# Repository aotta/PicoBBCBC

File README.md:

# PicoBBCBC
A BBC Bridge Companion Multicart based on Pico clone

This project allows you to bypass the original system constraints and load multiple ROMs onto the console using an interactive Z80 Assembly frontend menu and smart address-bus monitoring for seamless bank-switching.

---

## Hardware Gallery

Here is the hardware implementation of the multicart PCB and assembly:

| Cartridge PCB | Fully Assembled Unit |
|:---:|:---:|
|  |  |

*(Note: Please ensure your image filenames inside the `pictures/` folder match `pcb.jpg` and `assembled.jpg`, or update the paths above accordingly!)*

---

## How It Works

1. **The Z80 Frontend Menu**: Upon boot, a custom splash screen and menu written in pure Z80 Assembly initializes the TMS9129 VDP (Video Display Processor) and the Z80PIO chip.
2. **Menu Navigation**: The console's dedicated keyboard matrix is scanned continuously.
   * Press **PASS** to scroll **UP**.
   * Press **SPADES ** to scroll **DOWN**.
   * Press **CLUBS (** to **SELECT/START** the highlighted game.
3. **Address-Bus Triggering**: Once a game is selected, the cursor flashes as a confirmation feedback. The Z80 CPU then enters a tight loop, constantly reading from a specific ROM address range:
   \[\text{Target Address} = \$5000 + \text{Game Index (0-8)}\]
4. **Pico Bank-Switching**: The Raspberry Pi Pico acts as a bus sniffer. It detects the continuous read cycles (`MREQ` and `RD` active) on the targeted address within the `$7000–$7008` window. It instantly switches the memory bank to the selected game ROM and triggers a hardware reset to boot the new title.

---
## IMPORTANT NOTE: by mistake, I designed the edge connector REVERSED, so the cartridge *MUST* be inserted with pico facing down!

## Project Structure

The repository is organized as follows:
* `/PicoBBCBC`: Contains the `.ino` firmware source code for the Raspberry Pi Pico.
* `/PCB`: Contains the design files, schematics, and layouts for manufacturing the custom cartridge board.
* `/roms`: Storage directory for compiling and organizing the game binary files.
* `/pictures`: Images and visual documentation of the project.

---

## Compilation & Installation

### Z80 Menu Compilation
To assemble the menu source code (`splash.asm`), use the `gasm80` assembler:
```bash
gasm80 splash.asm -o splash.bin
```

### Pico Firmware
1. First time, flash must be formatted and ROM loaded. So, only the first time, you must upoad on pico the FW **`PicoBBCBC_FirstRun.uf2`**.
2. Format the flash RAM when asked by window and then load the ROMs **with the same name i used in the ROM folder** (the filenames are hardcoded in FW).
3. Now, you have to **reflash the Pico with the FW ad on pico the FW **`PicoBBCBC.ino.uf2`**.
4. Enjoy your multicart.

---

## License
This project is licensed under the GPL-3.0 License - see the [LICENSE](LICENSE) file for details.

## Acknowledgments
* Special thanks to **Leaded Solder** for the extensive reverse engineering documentation on the BBC Bridge Companion VDP registers, Z80PIO matrix structures, and stack pointer layout.

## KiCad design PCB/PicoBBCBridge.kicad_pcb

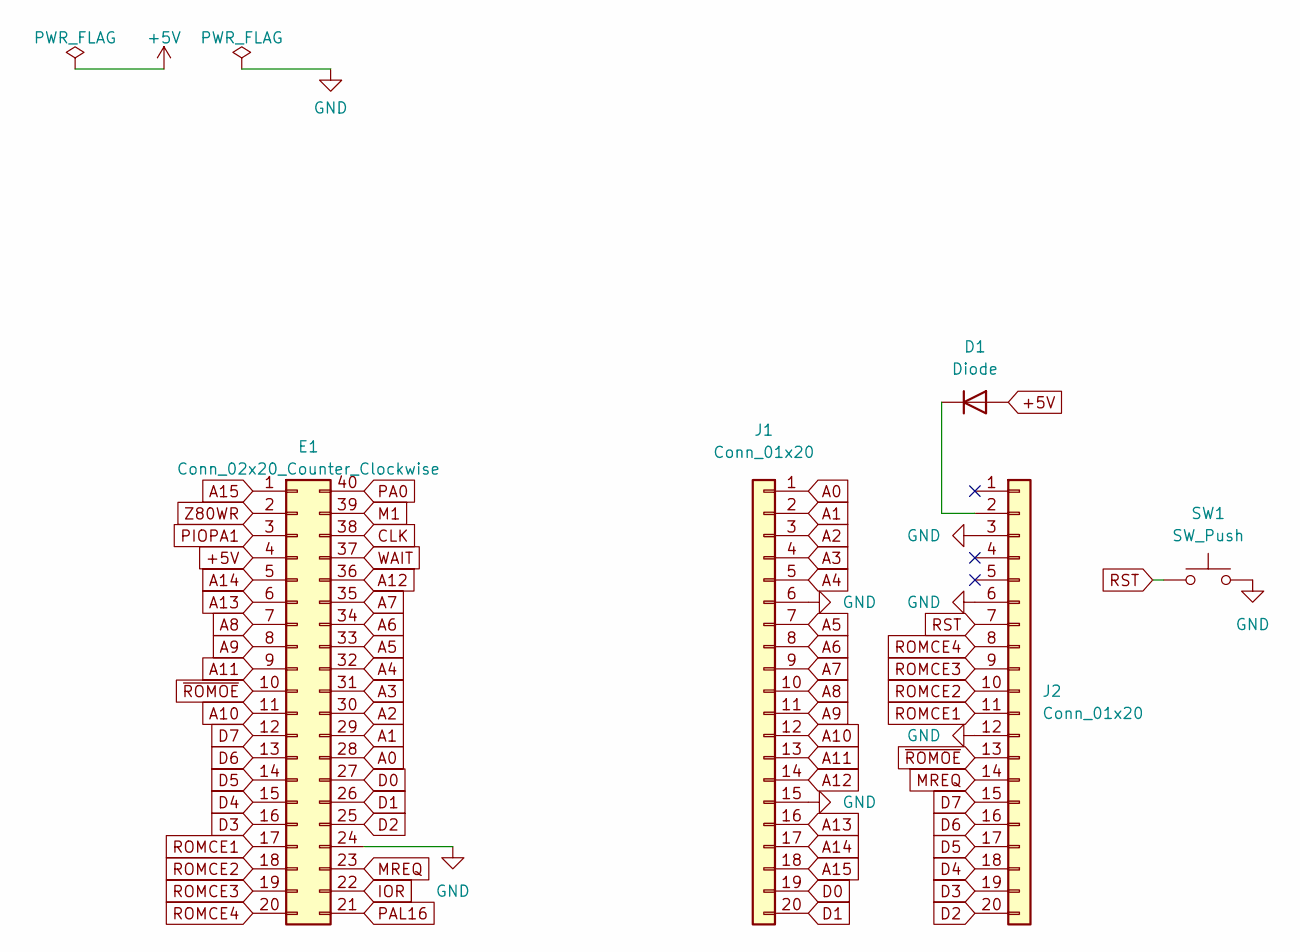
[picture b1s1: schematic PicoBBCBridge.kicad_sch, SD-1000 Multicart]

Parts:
D1: Diode; D_DO-35_SOD27_P7.62mm_Horizontal
E1: Conn_02x20_Counter_Clockwise; BBC_Bridge_Companion_Edge_40Pin
J1, J2: Conn_01x20; PinSocket_1x20_P2.54mm_Vertical
SW1: SW_Push; SW_PUSH_6mm

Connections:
+5V: D1.2 (A), E1.4
A0: E1.28, J1.1
A1: E1.29, J1.2
A2: E1.30, J1.3
A3: E1.31, J1.4
A4: E1.32, J1.5
A5: E1.33, J1.7
A6: E1.34, J1.8
A7: E1.35, J1.9
A8: E1.7, J1.10
A9: E1.8, J1.11
A10: E1.11, J1.12
A11: E1.9, J1.13
A12: E1.36, J1.14
A13: E1.6, J1.16
A14: E1.5, J1.17
A15: E1.1, J1.18
CLK: E1.38
D0: E1.27, J1.19
D1: E1.26, J1.20
D2: E1.25, J2.20
D3: E1.16, J2.19
D4: E1.15, J2.18
D5: E1.14, J2.17
D6: E1.13, J2.16
D7: E1.12, J2.15
GND: E1.24, J1.6, J1.15, J2.3, J2.6, J2.12, SW1.2
IOR: E1.22
M1: E1.39
MREQ: E1.23, J2.14
unnamed: D1.1 (K), J2.2
PA0: E1.40
PAL16: E1.21
PIOPA1: E1.3
ROMCE1: E1.17, J2.11
ROMCE2: E1.18, J2.10
ROMCE3: E1.19, J2.9
ROMCE4: E1.20, J2.8
RST: J2.7, SW1.1
WAIT: E1.37
Z80WR: E1.2
~ROMOE: E1.10, J2.13

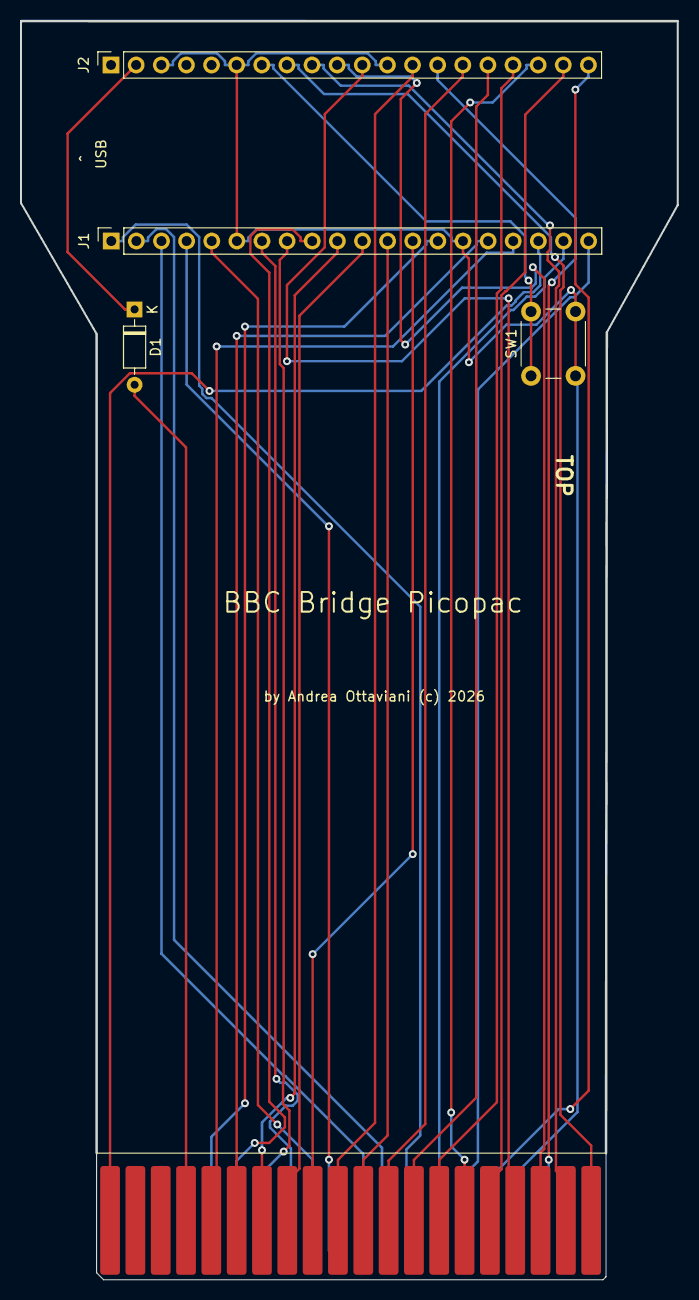
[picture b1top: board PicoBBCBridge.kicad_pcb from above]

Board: 2 copper layers, 66.4 x 127.3 mm, 5 parts (0 on the bottom side), 34 nets.

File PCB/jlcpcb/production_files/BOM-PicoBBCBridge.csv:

Comment,Designator,Footprint,LCSC,Quantity
SW_Push,SW1,SW_PUSH_6mm,,1
Conn_01x20,J1,PinSocket_1x20_P2.54mm_Vertical,,1
Diode,D1,D_DO-35_SOD27_P7.62mm_Horizontal,,1
Conn_01x20,J2,PinSocket_1x20_P2.54mm_Vertical,,1
Conn_02x20_Counter_Clockwise,E1,BBC_Bridge_Companion_Edge_40Pin,,1

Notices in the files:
PCB/PicoBBCBridge.kicad_pcb:
by Andrea Ottaviani (c) 2026
